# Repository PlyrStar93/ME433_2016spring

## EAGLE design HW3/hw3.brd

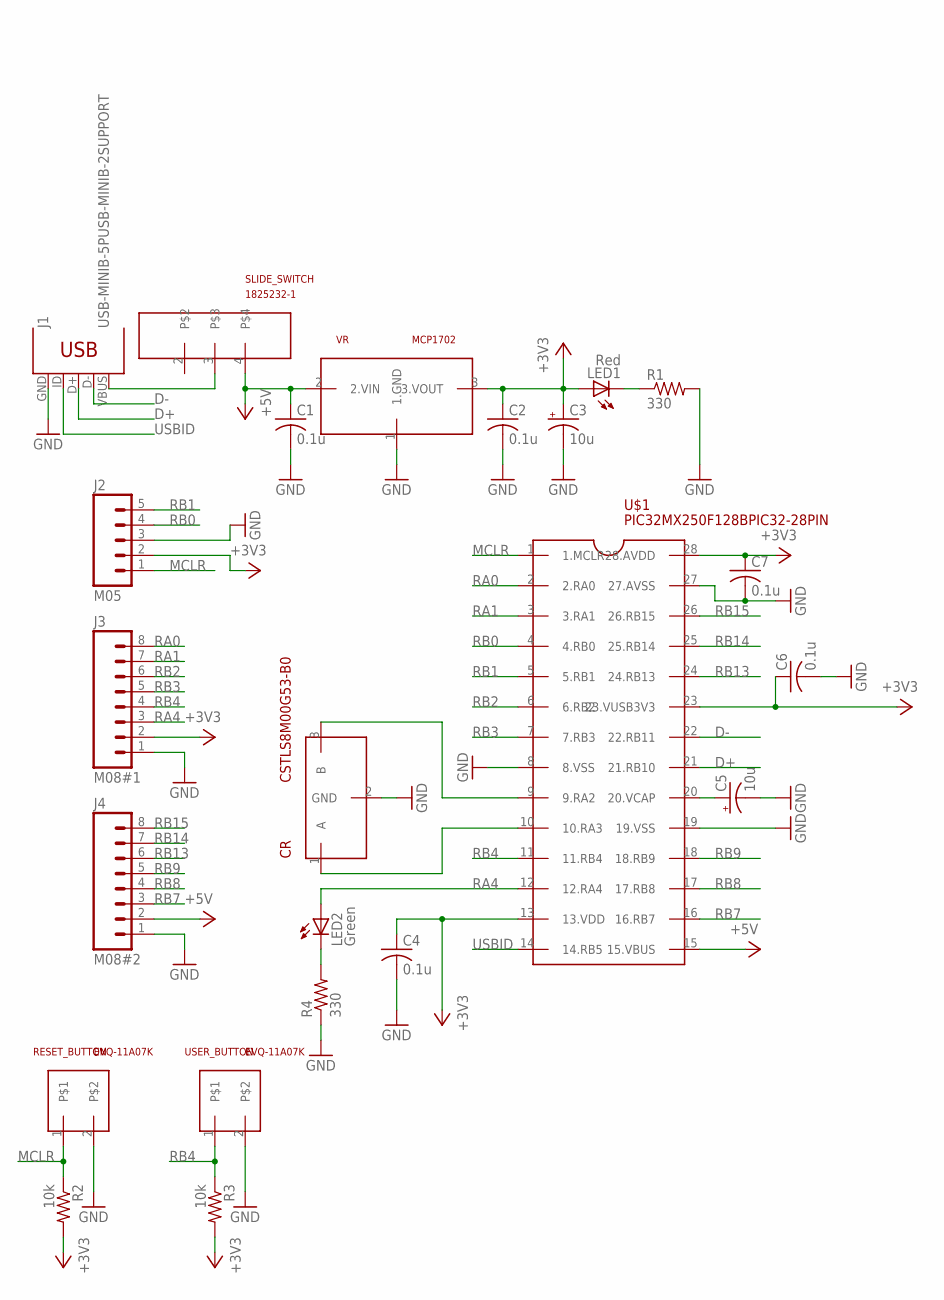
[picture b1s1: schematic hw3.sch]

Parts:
C1, C2, C4, C6, C7: 0.1u; C025-025X050
C3, C5: 10u; B45181A
CR: CSTLS8M00G53-B0; 1X03_NO_SILK
J1: USB-MINIB-5PUSB-MINIB-2SUPPORT; USB-MB-H
J2: M05; 1X05_NO_SILK
J3: M08#1; 1X08_ROUND
J4: M08#2; 1X08_ROUND
LED1: Red; LED3MM
LED2: Green; LED3MM
R1, R4: 330; 0207/10
R2, R3: 10k; 0207/10
RESET_BUTTON: EVQ-11A07K; 1X02_NO_SILK_FAR_BOUNDED
SLIDE_SWITCH: 1825232-1; 1X05_SLIDESWITCH
U$1: PIC32MX250F128BPIC32-28PIN; DIL28-3
USER_BUTTON: EVQ-11A07K; 1X02_NO_SILK_FAR_BOUNDED
VR: MCP1702; TO92

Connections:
+3V3: C2.1, C3.+, C4.1, C6.1, C7.1, J2.2, J3.2, LED1.A, R2.2, R3.2, U$1.13 (13.VDD), U$1.23 (23.VUSB3V3), U$1.28 (28.AVDD), VR.3 (3.VOUT)
+5V: C1.1, J4.2, SLIDE_SWITCH.4, U$1.15 (15.VBUS), VR.2 (2.VIN)
D+: J1.D+, U$1.21 (21.RB10)
D-: J1.D-, U$1.22 (22.RB11)
GND: C1.2, C2.2, C3.-, C4.2, C5.-, C6.2, C7.2, CR.2 (GND), J1.GND, J2.3, J3.1, J4.1, R1.2, R4.1, RESET_BUTTON.2, U$1.8 (8.VSS), U$1.19 (19.VSS), U$1.27 (27.AVSS), USER_BUTTON.2, VR.1 (1.GND)
MCLR: J2.1, R2.1, RESET_BUTTON.1, U$1.1 (1.MCLR)
unnamed: LED2.K (C), R4.2
unnamed: C5.+, U$1.20 (20.VCAP)
unnamed: LED1.K (C), R1.1
unnamed: J1.VBUS, SLIDE_SWITCH.3
unnamed: CR.3 (B), U$1.9 (9.RA2)
unnamed: CR.1 (A), U$1.10 (10.RA3)
RA0: J3.8, U$1.2 (2.RA0)
RA1: J3.7, U$1.3 (3.RA1)
RA4: J3.3, LED2.A, U$1.12 (12.RA4)
RB0: J2.4, U$1.4 (4.RB0)
RB1: J2.5, U$1.5 (5.RB1)
RB2: J3.6, U$1.6 (6.RB2)
RB3: J3.5, U$1.7 (7.RB3)
RB4: J3.4, R3.1, U$1.11 (11.RB4), USER_BUTTON.1
RB7: J4.3, U$1.16 (16.RB7)
RB8: J4.4, U$1.17 (17.RB8)
RB9: J4.5, U$1.18 (18.RB9)
RB13: J4.6, U$1.24 (24.RB13)
RB14: J4.7, U$1.25 (25.RB14)
RB15: J4.8, U$1.26 (26.RB15)
USBID: J1.ID, U$1.14 (14.RB5)

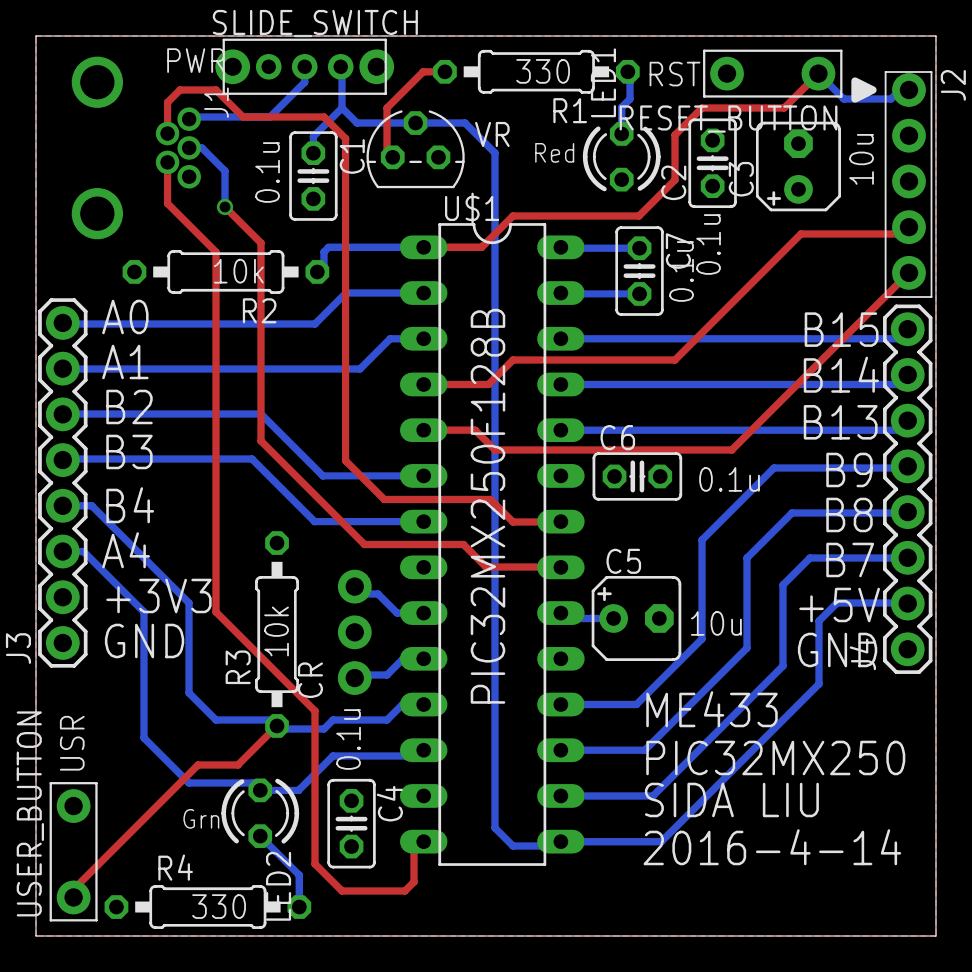
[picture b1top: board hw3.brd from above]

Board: 2 copper layers, 50.0 x 50.0 mm, 23 parts (0 on the bottom side), 27 nets.

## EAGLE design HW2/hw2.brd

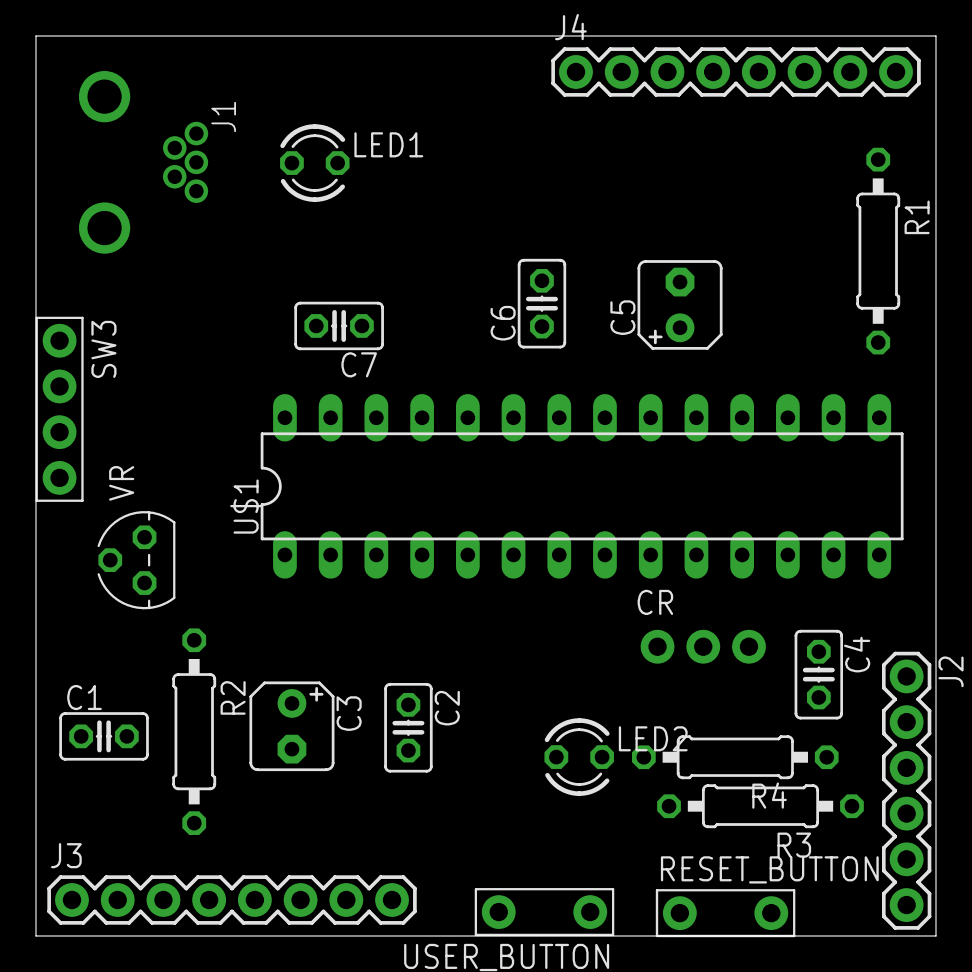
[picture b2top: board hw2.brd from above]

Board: 2 copper layers, 50.0 x 50.0 mm, 23 parts (0 on the bottom side), 27 nets, no tracks yet.

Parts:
C1, C2, C4, C6, C7: 0.1u; C025-025X050
C3, C5: 10u; B45181A
CR: CSTLS8M00G53-B0; 1X03_NO_SILK
J1: USB-MINIB-5PUSB-MINIB-2SUPPORT; USB-MB-H
J2: 1X06
J3, J4: 1X08_ROUND
LED1: Red; LED3MM
LED2: Green; LED3MM
R1, R4: 330; 0207/10
R2, R3: 10k; 0207/10
RESET_BUTTON: EVQ-11A07K; 1X02_NO_SILK_FAR_BOUNDED
SW3: 1825232-1PUSH_BUTTON_2SUPPORT; 1X04_NO_SILK_ALL_ROUND_BOUNDED
U$1: PIC32MX250F128BPIC32-28PIN; DIL28-3
USER_BUTTON: EVQ-11A07K; 1X02_NO_SILK_FAR_BOUNDED
VR: MCP1702; TO92

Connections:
+3V3: C2.1, C3.+, C4.1, C6.1, C7.2, J2.5, J3.7, LED1.A, R2.1, R3.1, U$1.13, U$1.23, U$1.28, VR.3
+5V: C1.1, J4.7, SW3.4, U$1.15, VR.2
GND: C1.2, C2.2, C3.-, C4.2, C5.-, C6.2, C7.1, CR.2, J1.GND, J2.4, J3.8, J4.8, R1.2, R4.1, RESET_BUTTON.1, U$1.8, U$1.19, U$1.27, USER_BUTTON.1, VR.1
unnamed: J1.ID, U$1.14
unnamed: J1.D+, U$1.21
unnamed: LED1.K, R1.1
unnamed: J1.VBUS, SW3.1
unnamed: J1.D-, U$1.22
unnamed: J2.2, U$1.5
unnamed: J2.6, R2.2, RESET_BUTTON.2, U$1.1
unnamed: J2.3, U$1.4
unnamed: CR.1, U$1.9
unnamed: J3.5, R3.2, U$1.11, USER_BUTTON.2
unnamed: CR.3, U$1.10
unnamed: J3.6, LED2.A, U$1.12
unnamed: LED2.K, R4.2
unnamed: C5.+, U$1.20
unnamed: J3.1, U$1.2
unnamed: J3.2, U$1.3
unnamed: J3.3, U$1.6
unnamed: J3.4, U$1.7
unnamed: J4.1, U$1.26
unnamed: J4.2, U$1.25
unnamed: J4.3, U$1.24
unnamed: J4.4, U$1.18
unnamed: J4.5, U$1.17
unnamed: J4.6, U$1.16

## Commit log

2016-04-04 Ford B100 lab access
2016-04-04 new folder
    create folder HW1
2016-04-04 Oscillation situations before/after adding capacitors
    Oscillation for voltage regulator shown in the image.
    Adding .1 uF on input Vin = no change;
    Adding .1 uF on output Vout = eliminate oscillation.
2016-04-04 Voltage regulator, resonator
    Voltage regulator with capacitors installed; resonator connected to chip.
2016-04-04 PIC32 circuit
    Completed PIC32 circuit.
2016-04-04 code template
2016-04-04 Create new project
    New MBLAB X Project created
2016-04-04 main.c main code
    Created new program file.
2016-04-04 DEVCFG0 register configurations
    DEVCFG0 register configurations for main.c
2016-04-04 DEVCFG2
    DEVCFG2 register configuration
2016-04-04 DEVCFG2
2016-04-04 DEVCFG3
2016-04-04 preliminary tests
2016-04-04 comment added for prelim codes
2016-04-04 RB4 if/else by push button
2016-04-04 Blink 1 Hz code (working)
2016-04-04 LED is now at 1kHz
    Per the homework requirement, the LED now blinks at 1 kHz, which means
    it will show as constantly light up even it's actually blinking.
2016-04-04 tab format
2016-04-04 PIC32 LED
    When the green LED blinks, it almost looks like being lit up constantly.
2016-04-04 move files
2016-04-05 Circuit diagram
2016-04-06 new folder
2016-04-07 Created HW2 EAGLE project
    Created HW2 EAGLE project
2016-04-07 Library - voltage regulator finished
2016-04-07 .sch almost done
2016-04-07 schematics
2016-04-11 new schematic and library
    The schematic has been improved.
2016-04-12 brd file created
2016-04-12 Board layout drawn, top and bottom
2016-04-14 Gerber files created; will need to change layout
    Due to the new layout regulation, I will have to edit the layout a
    little bit, even though the gerber files are here.
2016-04-14 rename HW3
2016-04-14 Redesigned schematic and board
2016-04-14 Ready to be checked before order
    Gerber generated; final modification on text and silk top
2016-04-14 Please use HW3 for final board design and ordering
    Please use HW3 for final board design and ordering
2016-06-09 hw10,hw11
2016-06-09 images
2016-06-09 sync issues
2016-06-09 hw_android
2016-06-09 slidebar
2016-06-09 slide bar with progress
    slide bar with progress
2016-06-09 hw9-images
2016-06-09 wheel test
2016-06-10 initial-hw8
    rt
2016-06-10 edited the code
2016-06-10 hw8-putty-screencap
2016-06-10 android-camera-app
2016-06-10 android-cdc
